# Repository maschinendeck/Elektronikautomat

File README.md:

# Elektronikautomat

Hardware und Software des Elekronikautomaten des Maschinendecks.
[Projektseite](https://github.com/maschinendeck/kanban/issues/2)
[Wiki Seite](https://wiki.maschinendeck.org/wiki/Zigarettenautomat)

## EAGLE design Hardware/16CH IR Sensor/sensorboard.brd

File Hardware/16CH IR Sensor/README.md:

# IR Sensor Board

Sensor board for measuring if there are any items left in a vending machine slot. Uses cheap TCRT5000 sensors. CAD Software used is EAGLE.

The IR LEDs of the sensors are driven by a serial shift register input, the combined analog output signal of all phototransistors is provided as an analog output with an internal pulldown resistor (configurable via pot).

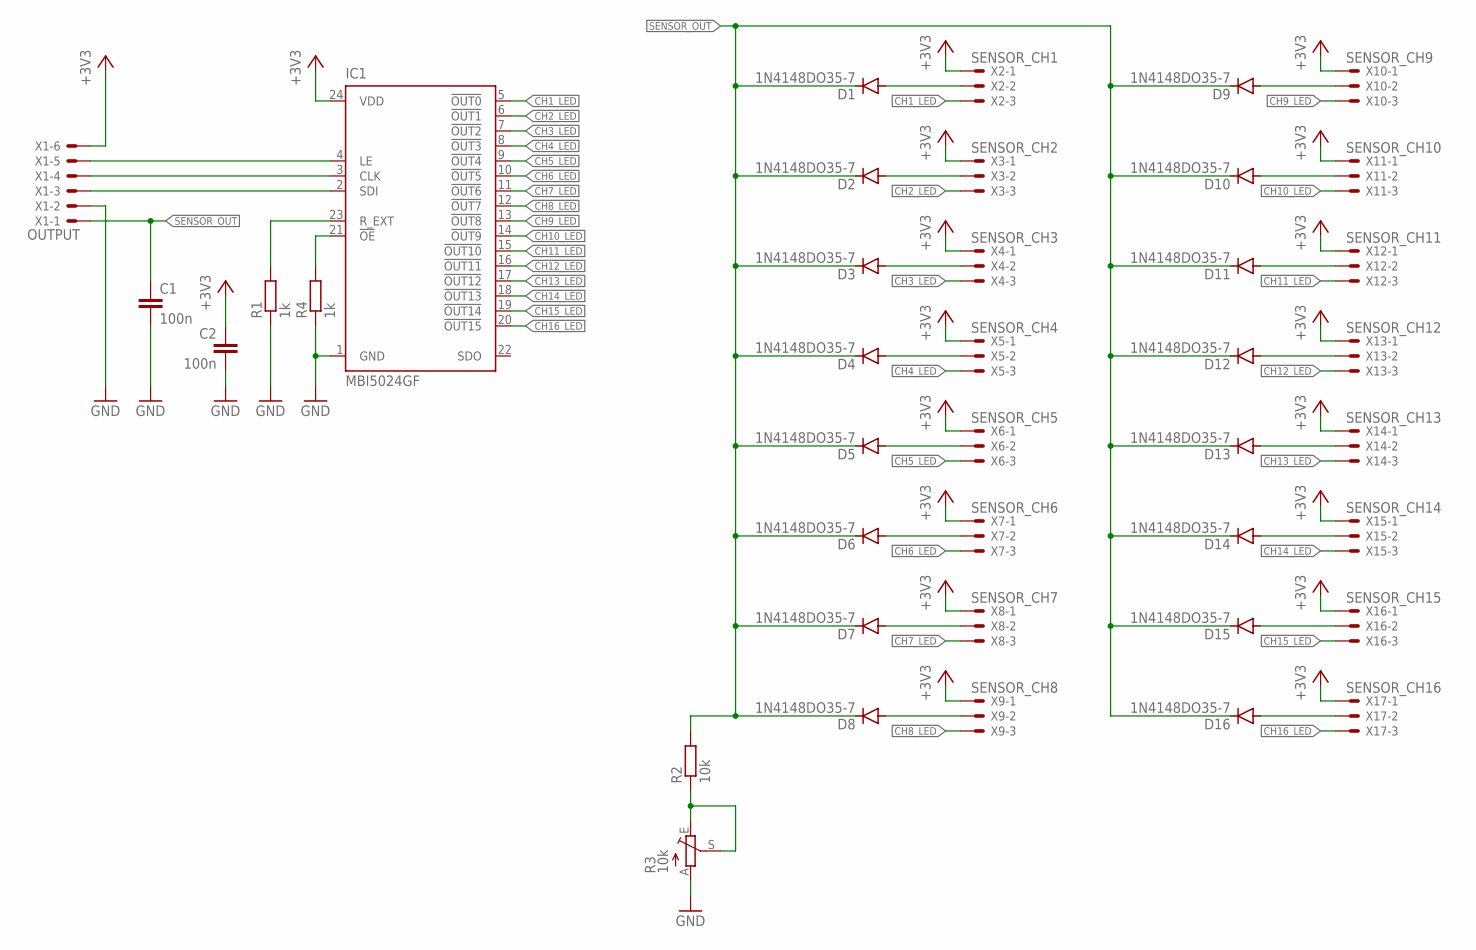
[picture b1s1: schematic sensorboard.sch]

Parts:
C1, C2: 100n; C050-024X044
D1, D2, D3, D4, D5, D6, D7, D8, D9, D10, D11, D12, D13, D14, D15, D16: 1N4148DO35-7; DO35-7
IC1: MBI5024GF; 24PIN_SOP_ADAPTER
R1, R4: 1k; 0207/10
R2: 10k; 0207/10
R3: 10k; CA6V
X1: OUTPUT; 22-23-2061
X2: SENSOR_CH1; 22-23-2031
X3: SENSOR_CH2; 22-23-2031
X4: SENSOR_CH3; 22-23-2031
X5: SENSOR_CH4; 22-23-2031
X6: SENSOR_CH5; 22-23-2031
X7: SENSOR_CH6; 22-23-2031
X8: SENSOR_CH7; 22-23-2031
X9: SENSOR_CH8; 22-23-2031
X10: SENSOR_CH9; 22-23-2031
X11: SENSOR_CH10; 22-23-2031
X12: SENSOR_CH11; 22-23-2031
X13: SENSOR_CH12; 22-23-2031
X14: SENSOR_CH13; 22-23-2031
X15: SENSOR_CH14; 22-23-2031
X16: SENSOR_CH15; 22-23-2031
X17: SENSOR_CH16; 22-23-2031

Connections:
+3V3: C2.1, IC1.24 (VDD), X1.6, X2.1, X3.1, X4.1, X5.1, X6.1, X7.1, X8.1, X9.1, X10.1, X11.1, X12.1, X13.1, X14.1, X15.1, X16.1, X17.1
CH1_LED: IC1.5 (!OUT0), X2.3
CH1_SENS: D1.A, X2.2
CH2_LED: IC1.6 (!OUT1), X3.3
CH2_SENS: D2.A, X3.2
CH3_LED: IC1.7 (!OUT2), X4.3
CH3_SENS: D3.A, X4.2
CH4_LED: IC1.8 (!OUT3), X5.3
CH4_SENS: D4.A, X5.2
CH5_LED: IC1.9 (!OUT4), X6.3
CH5_SENS: D5.A, X6.2
CH6_LED: IC1.10 (!OUT5), X7.3
CH6_SENS: D6.A, X7.2
CH7_LED: IC1.11 (!OUT6), X8.3
CH7_SENS: D7.A, X8.2
CH8_LED: IC1.12 (!OUT7), X9.3
CH8_SENS: D8.A, X9.2
CH9_LED: IC1.13 (!OUT8), X10.3
CH9_SENS: D9.A, X10.2
CH10_LED: IC1.14 (!OUT9), X11.3
CH10_SENS: D10.A, X11.2
CH11_LED: IC1.15 (!OUT10), X12.3
CH11_SENS: D11.A, X12.2
CH12_LED: IC1.16 (!OUT11), X13.3
CH12_SENS: D12.A, X13.2
CH13_LED: IC1.17 (!OUT12), X14.3
CH13_SENS: D13.A, X14.2
CH14_LED: IC1.18 (!OUT13), X15.3
CH14_SENS: D14.A, X15.2
CH15_LED: IC1.19 (!OUT14), X16.3
CH15_SENS: D15.A, X16.2
CH16_LED: IC1.20 (!OUT15), X17.3
CH16_SENS: D16.A, X17.2
GND: C1.2, C2.2, IC1.1 (GND), R1.1, R3.A, R4.1, X1.2
unnamed: IC1.4 (LE), X1.5
unnamed: IC1.23 (R_EXT), R1.2
unnamed: R2.1, R3.E, R3.S
unnamed: IC1.3 (CLK), X1.4
unnamed: IC1.2 (SDI), X1.3
unnamed: IC1.21 (!OE), R4.2
SENSOR_OUT: C1.1, D1.C, D2.C, D3.C, D4.C, D5.C, D6.C, D7.C, D8.C, D9.C, D10.C, D11.C, D12.C, D13.C, D14.C, D15.C, D16.C, R2.2, X1.1

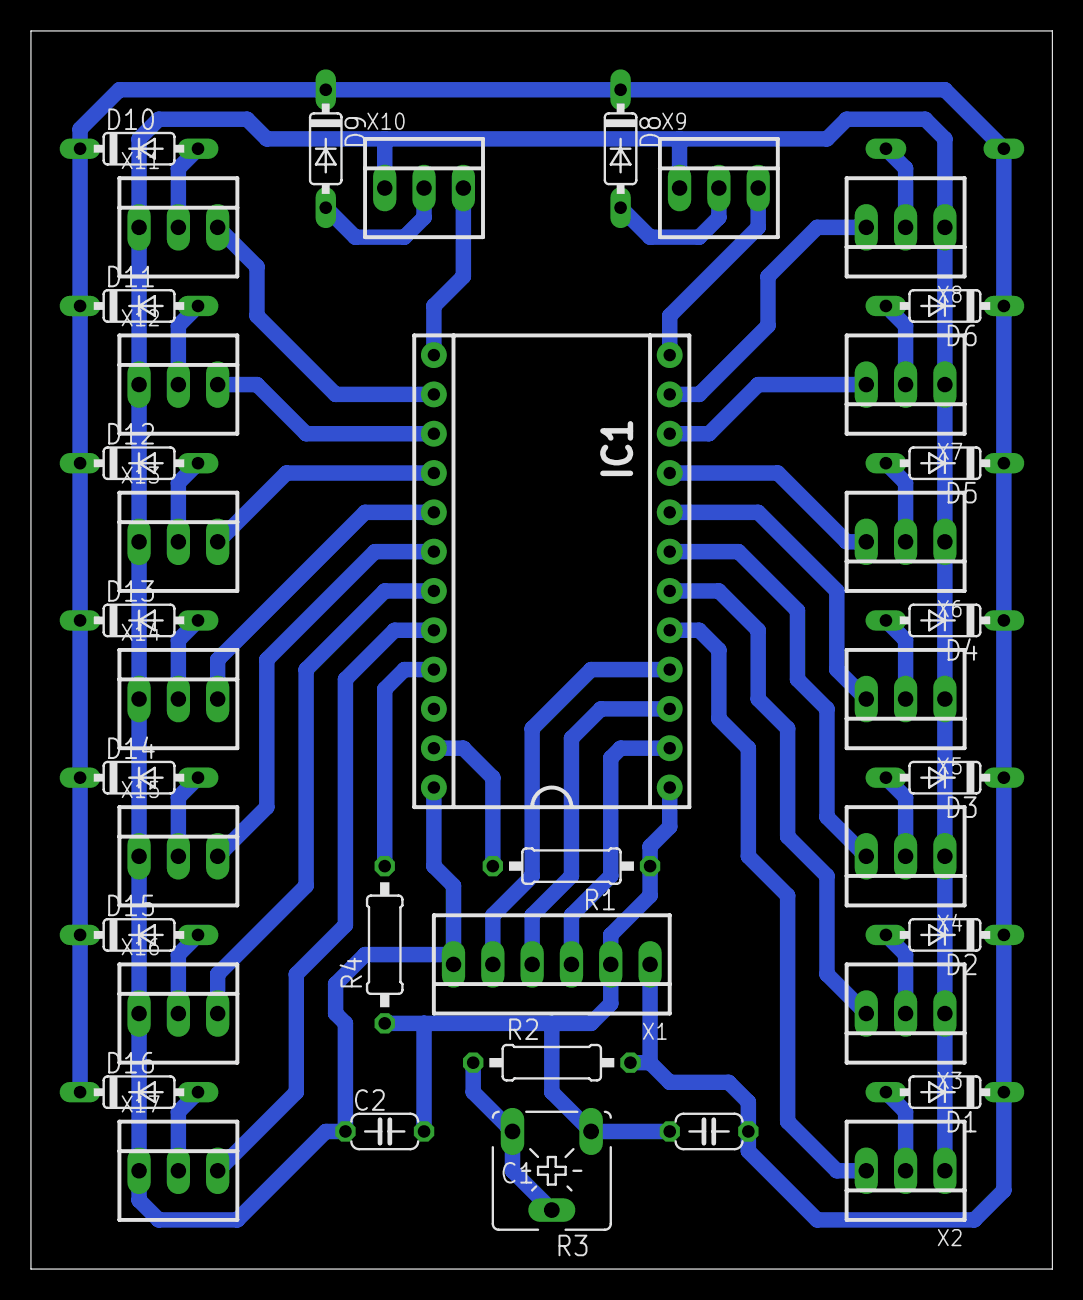
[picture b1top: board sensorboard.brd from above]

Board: 2 copper layers, 66.0 x 80.0 mm, 40 parts (1 on the bottom side), 41 nets.

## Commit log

2021-11-25 added readme file
2021-11-25 added cover images
2021-11-25 added mqtt function
2021-11-26 Modified Firmware to just do RGB display for now, sensors will be added later
2021-12-11 fixed LEDs (hardware problem), added sensors and mqtt
2021-12-14 added second set of WS2812 LEDs on bottom (currently fading blue leds)
2021-12-19 added fire animation, fixed brightness
2023-04-20 updated cover pictures
2023-04-21 added coverpictures and price tag
2023-06-10 got the sensors of the first 5 channels working, other channels are hardcoded
